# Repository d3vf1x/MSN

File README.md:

# MSN (Multiprotocol Sensor Node)

Wireless Enviromental Sensor that can make use of multiple IoT technologies.

## Software

## Runtime

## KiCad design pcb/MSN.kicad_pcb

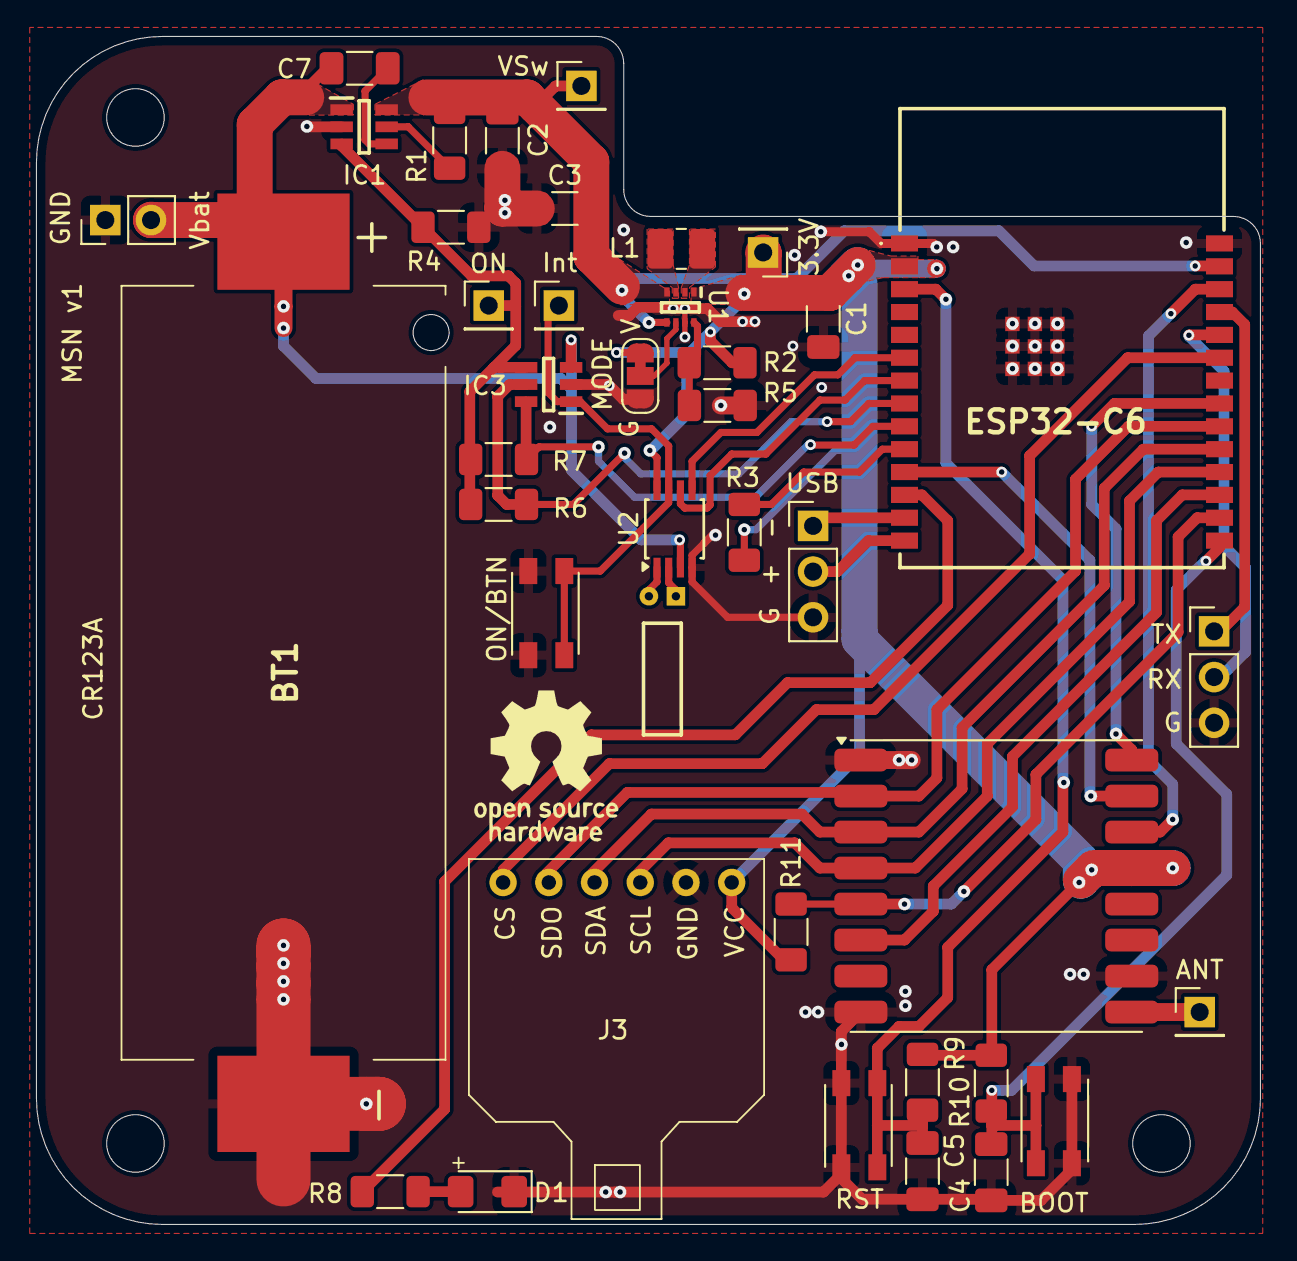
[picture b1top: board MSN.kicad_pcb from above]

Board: 2 copper layers, 68.0 x 66.0 mm, 43 parts (0 on the bottom side), 37 nets.

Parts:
3.3V: Vout; PinHeader_1x01_P2.54mm_Vertical
ANT: ANT; PinHeader_1x01_P2.54mm_Vertical
BOOT: Boot; SW_Push_3x4x2.5
BT1: CR123a (BX0123); BatteryHolder_Eagle_CR123A_12BH23PGR
C1, C2: 47uF; C_1206_3216Metric_Pad1.33x1.80mm_HandSolder
C3: 22uF; C_1206_3216Metric_Pad1.33x1.80mm_HandSolder
C4, C5: 0.1uF; C_1206_3216Metric_Pad1.33x1.80mm_HandSolder
C7: C; C_1206_3216Metric_Pad1.33x1.80mm_HandSolder
D1: Debug 2.1V/20mA; LED_1206_3216Metric_Pad1.42x1.75mm_HandSolder
ESP32-C6: ESP32-C6-WROOM-1-N4; ESP32-C6-WROOM1-N4
H1, H2, H3: MountingHole; MountingHole_3.2mm_M3
IC1: TPS22917DBVT; SOT95P280X145-6N
IC3: MAX16150AUT+T; SOT95P280X145-6N
Int: INT; PinHeader_1x01_P2.54mm_Vertical
J3: TX/RX; PinHeader_1x03_P2.54mm_Vertical
J3#2: BME680; BME680_Board
JP1: Mode Select; SolderJumper-3_P1.3mm_Bridged12_RoundedPad1.0x1.5mm_NumberL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
JUSB: USB; PinHeader_1x03_P2.54mm_Vertical
L1: 1uH; L_1008_2520Metric_Pad1.43x2.20mm_HandSolder
ON: Out; PinHeader_1x01_P2.54mm_Vertical
ON/BTN: On/SW_2; SW_Push_3x4x2.5
R1: 0; R_1206_3216Metric_Pad1.30x1.75mm_HandSolder
R2: 91; R_1206_3216Metric_Pad1.30x1.75mm_HandSolder
R3, R9, R10, R11: 10K; R_1206_3216Metric_Pad1.30x1.75mm_HandSolder
R4, R6, R7: 10k; R_1206_3216Metric_Pad1.30x1.75mm_HandSolder
R5: 511; R_1206_3216Metric_Pad1.30x1.75mm_HandSolder
R8: 68; R_1206_3216Metric_Pad1.30x1.75mm_HandSolder
RST: RST; SW_Push_3x4x2.5
U1: TPS631000DRLR; SOTFL50P160X60-8N
U2: PCF85363ATT/A; TSSOP-8_3x3mm_P0.65mm
U3: RFM96W-315S2; HOPERF_RFM9XW_SMD
VSw: VSw; PinHeader_1x01_P2.54mm_Vertical
Vbat: VBat; PinHeader_1x02_P2.54mm_Vertical
Y1: AB26T/32,768kHz; Crystal_AB26T_Horizontal

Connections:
+3.3V: 3.3V.1, C1.1, ESP32-C6.2 (3V3), J3#2.6, JP1.1 (A), R2.2, R3.2, R9.2, R10.2, R11.2, U1.1 (VOUT), U2.8 (VDD), U3.13 (3.3V)
/ADC_CH2: C2.2, C3.2, ESP32-C6.27 (IO2), IC1.6 (VOUT), R1.2, U1.4 (VIN), U1.5 (EN), VSw.1
/BME_CS: ESP32-C6.23 (IO15), J3#2.1
/BTN_INT: ESP32-C6.8 (IO0), IC3.5 (~INT), R6.1
/Boot/SW_1: BOOT.2 (1), C5.2, ESP32-C6.15 (IO9), R10.1
/CLR: ESP32-C6.9 (IO1), IC3.6 (~CLR), R7.1
/EN: C4.2, ESP32-C6.3 (EN), R9.1, RST.2 (1)
/MISO: ESP32-C6.20 (IO22), J3#2.2, U3.2 (MISO)
/MOSI: ESP32-C6.19 (IO21), J3#2.3, U3.3 (MOSI)
/RF_DIO0: ESP32-C6.26 (IO3), U3.14 (DIO0)
/RF_DIO1: ESP32-C6.11 (IO10), U3.15 (DIO1)
/RF_DIO2: ESP32-C6.21 (IO23), U3.16 (DIO2)
/RF_NSS: ESP32-C6.16 (IO18), R11.1, U3.5 (NSS)
/RF_RST: ESP32-C6.17 (IO19), U3.6 (RESET)
/SCK: ESP32-C6.18 (IO20), J3#2.4, U3.4 (SCK)
/SCL: ESP32-C6.7 (IO7), U2.6 (SCL)
/SDA: ESP32-C6.6 (IO6), U2.5 (SDA)
/USB_D+: ESP32-C6.14 (IO13), JUSB.2
/USB_D-: ESP32-C6.13 (IO12), JUSB.1
GND: BOOT.1, BT1.2 (-), C1.2, C2.1, C3.1, C4.1, C5.1, D1.1 (K), ESP32-C6.1 (GND_1), ESP32-C6.28 (GND_2), ESP32-C6.29 (GND_3), ESP32-C6.30 (GND_4), ESP32-C6.31 (GND_5), ESP32-C6.32 (GND_6), ESP32-C6.33 (GND_7), ESP32-C6.34 (GND_8), ESP32-C6.35 (GND_9), ESP32-C6.36 (GND_10), ESP32-C6.37 (GND_11), IC1.2 (GND), IC3.2 (GND), J3.3, J3#2.5, JP1.3 (B), JUSB.3, ON/BTN.1, R4.2, R5.1, RST.1, U1.7 (GND), U2.4 (VSS), U3.1 (GND), U3.8 (GND), U3.10 (GND), Vbat.1
unnamed: D1.2 (A), R8.1
unnamed: C7.1, IC1.4 (CT)
unnamed: IC1.3 (ON), IC3.4 (OUT), ON.1, R4.1, R6.2, R7.2
unnamed: IC1.5 (QOD), R1.1
unnamed: ESP32-C6.10 (IO8), R3.1
unnamed: ESP32-C6.12 (IO11), R8.2
unnamed: ESP32-C6.24 (RXD0), J3.2
unnamed: ESP32-C6.25 (TXD0), J3.1
unnamed: IC3.1 (~PB_IN), Int.1, ON/BTN.2 (1), U2.7 (~INTA)
unnamed: ANT.1, U3.9 (ANT)
unnamed: JP1.2 (C), U1.6 (MODE)
unnamed: R2.1, R5.2, U1.8 (FB)
unnamed: L1.2, U1.3 (LX1)
unnamed: L1.1, U1.2 (LX2)
unnamed: U2.1 (OSCI), Y1.2
unnamed: U2.2 (OSCO), Y1.1
VBat: BT1.1 (+), C7.2, IC1.1 (VIN), IC3.3 (VCC), U2.3 (VBAT), Vbat.2

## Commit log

2024-10-23 Improve Readme and add code
2024-10-23 Cleanup
